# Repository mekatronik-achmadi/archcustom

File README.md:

# Arch Linux with MATE Desktop

My Personal lists, scripts, and configurations for my Arch Linux with MATE Desktop installation while try to be minimal as possible.

This repository store all my personal package lists, script, and configurations for my Arch Linux installation.
This also store many of development work notes.
If you find anything here to be useful, feel free to use as you like.

You can download and try the ISO example from [My SourceForge](https://sourceforge.net/projects/archlinux-custom-iso/files/archmate/)

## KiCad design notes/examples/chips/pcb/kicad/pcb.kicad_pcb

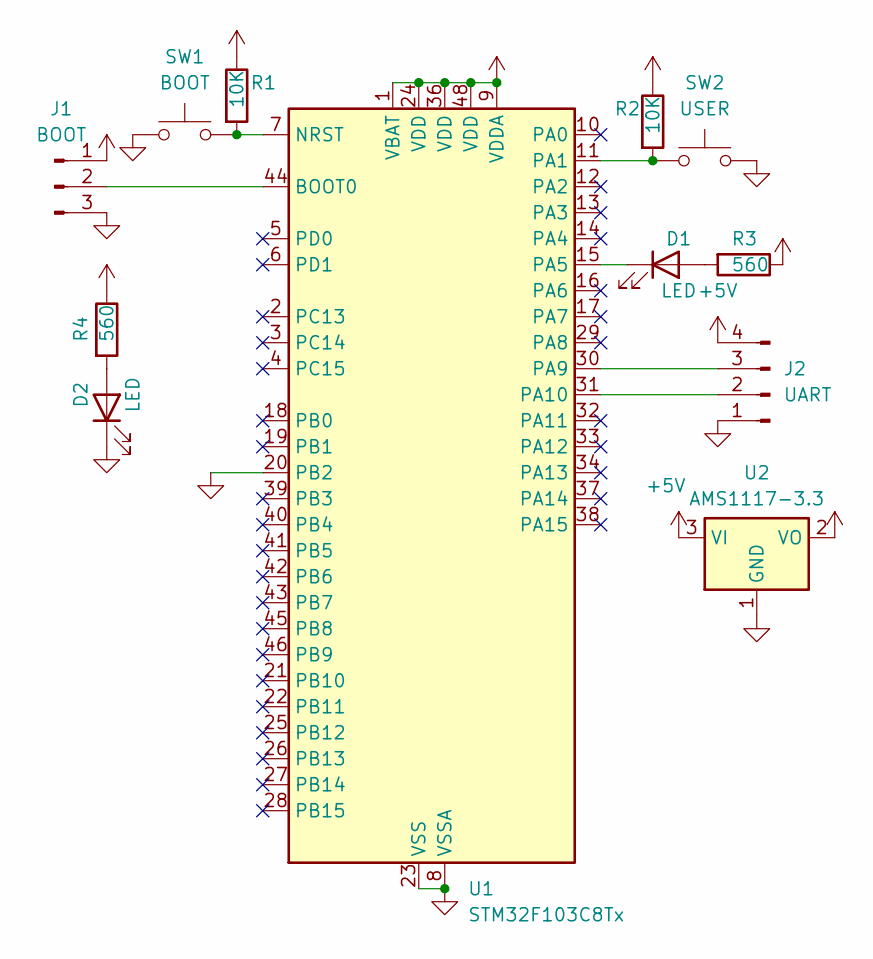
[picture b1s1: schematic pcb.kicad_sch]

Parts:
D1, D2: LED; LED_1206_3216Metric_Pad1.42x1.75mm_HandSolder
J1: BOOT; PinHeader_1x03_P2.54mm_Vertical
J2: UART; PinHeader_1x04_P2.54mm_Vertical
R1, R2: 10K; R_1206_3216Metric_Pad1.30x1.75mm_HandSolder
R3, R4: 560; R_1206_3216Metric_Pad1.30x1.75mm_HandSolder
SW1: BOOT; SW_SPST_B3U-1000P
SW2: USER; SW_SPST_B3U-1000P
U1: STM32F103C8Tx; LQFP-48_7x7mm_P0.5mm
U2: AMS1117-3.3; SOT-223-3_TabPin2

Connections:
+5V: J2.4, U2.3 (VI)
GND: D2.1 (K), J1.3, J2.1, SW1.1, SW2.2, U1.8 (VSSA), U1.20 (PB2), U1.23 (VSS), U1.35 (VSS), U1.47 (VSS), U2.1 (GND)
unnamed: D1.2 (A), R3.2
unnamed: D1.1 (K), U1.15 (PA5)
unnamed: D2.2 (A), R4.2
unnamed: J1.2, U1.44 (BOOT0)
unnamed: J2.2, U1.31 (PA10)
unnamed: J2.3, U1.30 (PA9)
unnamed: R1.2, SW1.2, U1.7 (NRST)
unnamed: R2.2, SW2.1, U1.11 (PA1)
VDD: J1.1, R1.1, R2.1, R3.1, R4.1, U1.1 (VBAT), U1.9 (VDDA), U1.24 (VDD), U1.36 (VDD), U1.48 (VDD), U2.2 (VO)

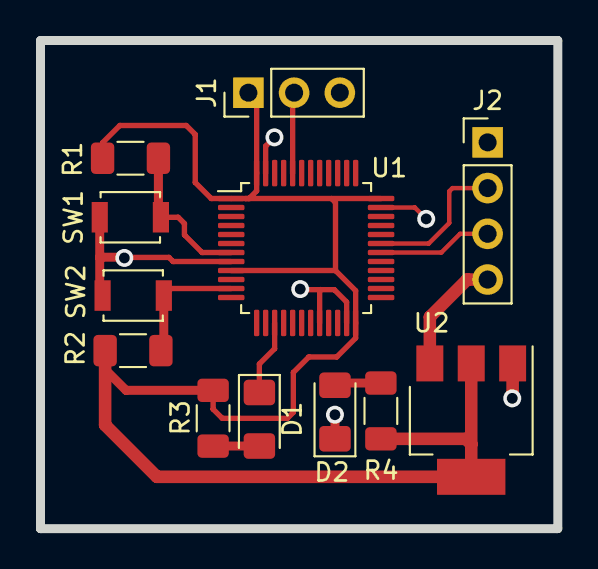
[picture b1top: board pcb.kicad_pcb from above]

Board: 2 copper layers, 28.7 x 27.1 mm, 12 parts (0 on the bottom side), 11 nets.

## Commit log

2024-08-12 Start New
2024-08-12 ArchISO
2024-08-12 ArchISO Script
2024-08-12 Custom Packages
2024-08-13 Arch Linux Custom
2024-08-13 ArchISO Notes
2024-08-13 Driver Lists
2024-08-13 Update Package List
2024-08-13 Design List
2024-08-13 Virtualization List
2024-08-13 Networking List
2024-08-13 Remove Multilib
2024-08-14 Electronic List
2024-08-14 College List
2024-08-14 Package Lists
2024-08-14 Remove Unused
2024-08-15 FreeCAD BoM
2024-08-16 LibreCAD
2024-08-16 CAD Tools
2024-08-17 Improve ArchISO
2024-08-17 Unused Package List
2024-08-17 Notes
2024-08-17 Pacman Notes
2024-08-17 Gerber Viewer
2024-08-17 BeagleBone
2024-08-17 Update ArchISO
2024-08-17 RaspberryPi Notes
2024-08-17 Raspi Drivers
2024-08-17 Raspi Notes
2024-08-17 Desktop Examples
2024-08-17 Desktop Programming Examples
2024-08-17 Chip Programming Example
2024-08-17 KiCAD Notes
2024-08-18 Remove URLs
2024-08-20 Fractals
2024-08-27 Update Package Lists
2024-08-29 Microsoft Packages
2024-09-07 Rework KiCAD Guide
2024-09-07 Drawing Sheet
2024-09-07 KiCAD Wiring
2024-09-07 KiCAD DXF
2024-09-07 KiCAD Drawing
2024-09-10 SVG to DXF
2024-09-15 Microsoft Egde and 365
2024-09-15 PCB Summary Guides
2024-09-16 Remove MS-365-Electron
2024-11-20 Update EDOPro Notes
2024-11-21 EDOPro Notes
2024-11-22 Update Notes EDOPro
2024-11-22 Update EDOPro (drop Android)
